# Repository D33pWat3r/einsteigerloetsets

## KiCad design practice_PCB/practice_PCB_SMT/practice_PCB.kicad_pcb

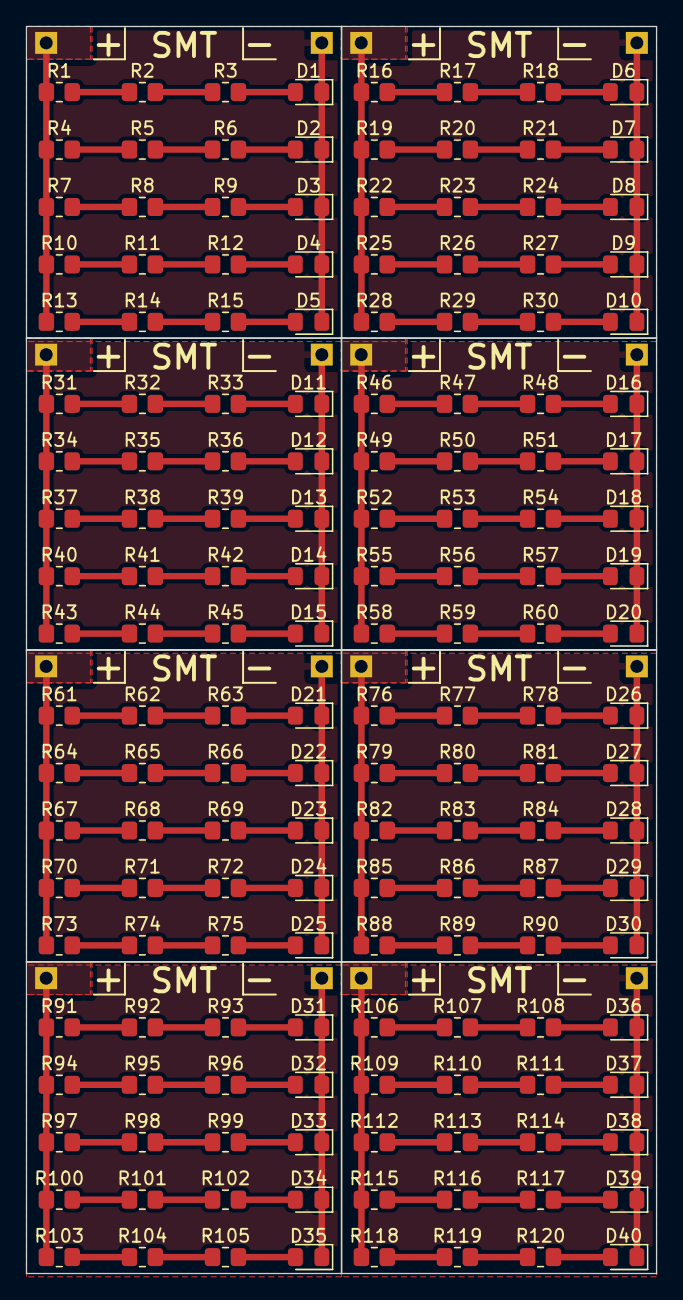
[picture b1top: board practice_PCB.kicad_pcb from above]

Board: 2 copper layers, 48.8 x 96.5 mm, 176 parts (0 on the bottom side), 17 nets.

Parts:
D1, D2, D3, D4, D5, D6, D7, D8, D9, D10, D11, D12, D13, D14, D15, D16, D17, D18, D19, D20, D21, D22, D23, D24, D25, D26, D27, D28, D29, D30, D31, D32, D33, D34, D35, D36, D37, D38, D39, D40: LED; LED_0805_2012Metric_Pad1.15x1.40mm_HandSolder
J1, J3, J5, J7, J9, J11, J13, J15: 5V; PinSocket_1x01_P2.54mm_Vertical
J2, J4, J6, J8, J10, J12, J14, J16: GND; PinSocket_1x01_P2.54mm_Vertical
R1, R2, R3, R4, R5, R6, R7, R8, R9, R10, R11, R12, R13, R14, R15, R16, R17, R18, R19, R20, R21, R22, R23, R24, R25, R26, R27, R28, R29, R30, R31, R32, R33, R34, R35, R36, R37, R38, R39, R40, R41, R42, R43, R44, R45, R46, R47, R48, R49, R50, R51, R52, R53, R54, R55, R56, R57, R58, R59, R60, R61, R62, R63, R64, R65, R66, R67, R68, R69, R70, R71, R72, R73, R74, R75, R76, R77, R78, R79, R80, R81, R82, R83, R84, R85, R86, R87, R88, R89, R90, R91, R92, R93, R94, R95, R96, R97, R98, R99, R100, R101, R102, R103, R104, R105, R106, R107, R108, R109, R110, R111, R112, R113, R114, R115, R116, R117, R118, R119, R120: 60; R_0805_2012Metric_Pad1.20x1.40mm_HandSolder

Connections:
+5V: J1.1, J3.1, J5.1, J7.1, J9.1, J11.1, J13.1, J15.1, R1.1, R4.1, R7.1, R10.1, R13.1, R16.1, R19.1, R22.1, R25.1, R28.1, R31.1, R34.1, R37.1, R40.1, R43.1, R46.1, R49.1, R52.1, R55.1, R58.1, R61.1, R64.1, R67.1, R70.1, R73.1, R76.1, R79.1, R82.1, R85.1, R88.1, R91.1, R94.1, R97.1, R100.1, R103.1, R106.1, R109.1, R112.1, R115.1, R118.1
GND: D1.1 (K), D2.1 (K), D3.1 (K), D4.1 (K), D5.1 (K), D6.1 (K), D7.1 (K), D8.1 (K), D9.1 (K), D10.1 (K), D11.1 (K), D12.1 (K), D13.1 (K), D14.1 (K), D15.1 (K), D16.1 (K), D17.1 (K), D18.1 (K), D19.1 (K), D20.1 (K), D21.1 (K), D22.1 (K), D23.1 (K), D24.1 (K), D25.1 (K), D26.1 (K), D27.1 (K), D28.1 (K), D29.1 (K), D30.1 (K), D31.1 (K), D32.1 (K), D33.1 (K), D34.1 (K), D35.1 (K), D36.1 (K), D37.1 (K), D38.1 (K), D39.1 (K), D40.1 (K), J2.1, J4.1, J6.1, J8.1, J10.1, J12.1, J14.1, J16.1
unnamed: D1.2 (A), D6.2 (A), D11.2 (A), D16.2 (A), D21.2 (A), D26.2 (A), D31.2 (A), D36.2 (A), R3.2, R18.2, R33.2, R48.2, R63.2, R78.2, R93.2, R108.2
unnamed: D2.2 (A), D7.2 (A), D12.2 (A), D17.2 (A), D22.2 (A), D27.2 (A), D32.2 (A), D37.2 (A), R6.2, R21.2, R36.2, R51.2, R66.2, R81.2, R96.2, R111.2
unnamed: D3.2 (A), D8.2 (A), D13.2 (A), D18.2 (A), D23.2 (A), D28.2 (A), D33.2 (A), D38.2 (A), R9.2, R24.2, R39.2, R54.2, R69.2, R84.2, R99.2, R114.2
unnamed: D4.2 (A), D9.2 (A), D14.2 (A), D19.2 (A), D24.2 (A), D29.2 (A), D34.2 (A), D39.2 (A), R12.2, R27.2, R42.2, R57.2, R72.2, R87.2, R102.2, R117.2
unnamed: D5.2 (A), D10.2 (A), D15.2 (A), D20.2 (A), D25.2 (A), D30.2 (A), D35.2 (A), D40.2 (A), R15.2, R30.2, R45.2, R60.2, R75.2, R90.2, R105.2, R120.2
unnamed: R1.2, R2.1, R16.2, R17.1, R31.2, R32.1, R46.2, R47.1, R61.2, R62.1, R76.2, R77.1, R91.2, R92.1, R106.2, R107.1
unnamed: R2.2, R3.1, R17.2, R18.1, R32.2, R33.1, R47.2, R48.1, R62.2, R63.1, R77.2, R78.1, R92.2, R93.1, R107.2, R108.1
unnamed: R4.2, R5.1, R19.2, R20.1, R34.2, R35.1, R49.2, R50.1, R64.2, R65.1, R79.2, R80.1, R94.2, R95.1, R109.2, R110.1
unnamed: R5.2, R6.1, R20.2, R21.1, R35.2, R36.1, R50.2, R51.1, R65.2, R66.1, R80.2, R81.1, R95.2, R96.1, R110.2, R111.1
unnamed: R7.2, R8.1, R22.2, R23.1, R37.2, R38.1, R52.2, R53.1, R67.2, R68.1, R82.2, R83.1, R97.2, R98.1, R112.2, R113.1
unnamed: R8.2, R9.1, R23.2, R24.1, R38.2, R39.1, R53.2, R54.1, R68.2, R69.1, R83.2, R84.1, R98.2, R99.1, R113.2, R114.1
unnamed: R10.2, R11.1, R25.2, R26.1, R40.2, R41.1, R55.2, R56.1, R70.2, R71.1, R85.2, R86.1, R100.2, R101.1, R115.2, R116.1
unnamed: R11.2, R12.1, R26.2, R27.1, R41.2, R42.1, R56.2, R57.1, R71.2, R72.1, R86.2, R87.1, R101.2, R102.1, R116.2, R117.1
unnamed: R13.2, R14.1, R28.2, R29.1, R43.2, R44.1, R58.2, R59.1, R73.2, R74.1, R88.2, R89.1, R103.2, R104.1, R118.2, R119.1
unnamed: R14.2, R15.1, R29.2, R30.1, R44.2, R45.1, R59.2, R60.1, R74.2, R75.1, R89.2, R90.1, R104.2, R105.1, R119.2, R120.1

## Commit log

2021-11-01 picture of the usb ghost pcbs
2021-11-01 add a ReadMe
2021-11-01 add PDF export of the manual
2022-05-13 Übungsplatine zum SMT Löten
2022-05-13 Übungsplatine zum THT Löten
2022-05-23 change the page layout and export to a pdf file
2022-05-23 fix some errors with the edge Cut Line
2022-05-23 make an array
2022-05-23 change page layout and export a pdf file
2022-05-23 create an array and copy the SMT Array in to the file
2022-05-23 create a Gerber File for Order
    the Gerber file includes:
    - 8x SMT Übungsplatinen
    - 8x THT Übungsplatinen
